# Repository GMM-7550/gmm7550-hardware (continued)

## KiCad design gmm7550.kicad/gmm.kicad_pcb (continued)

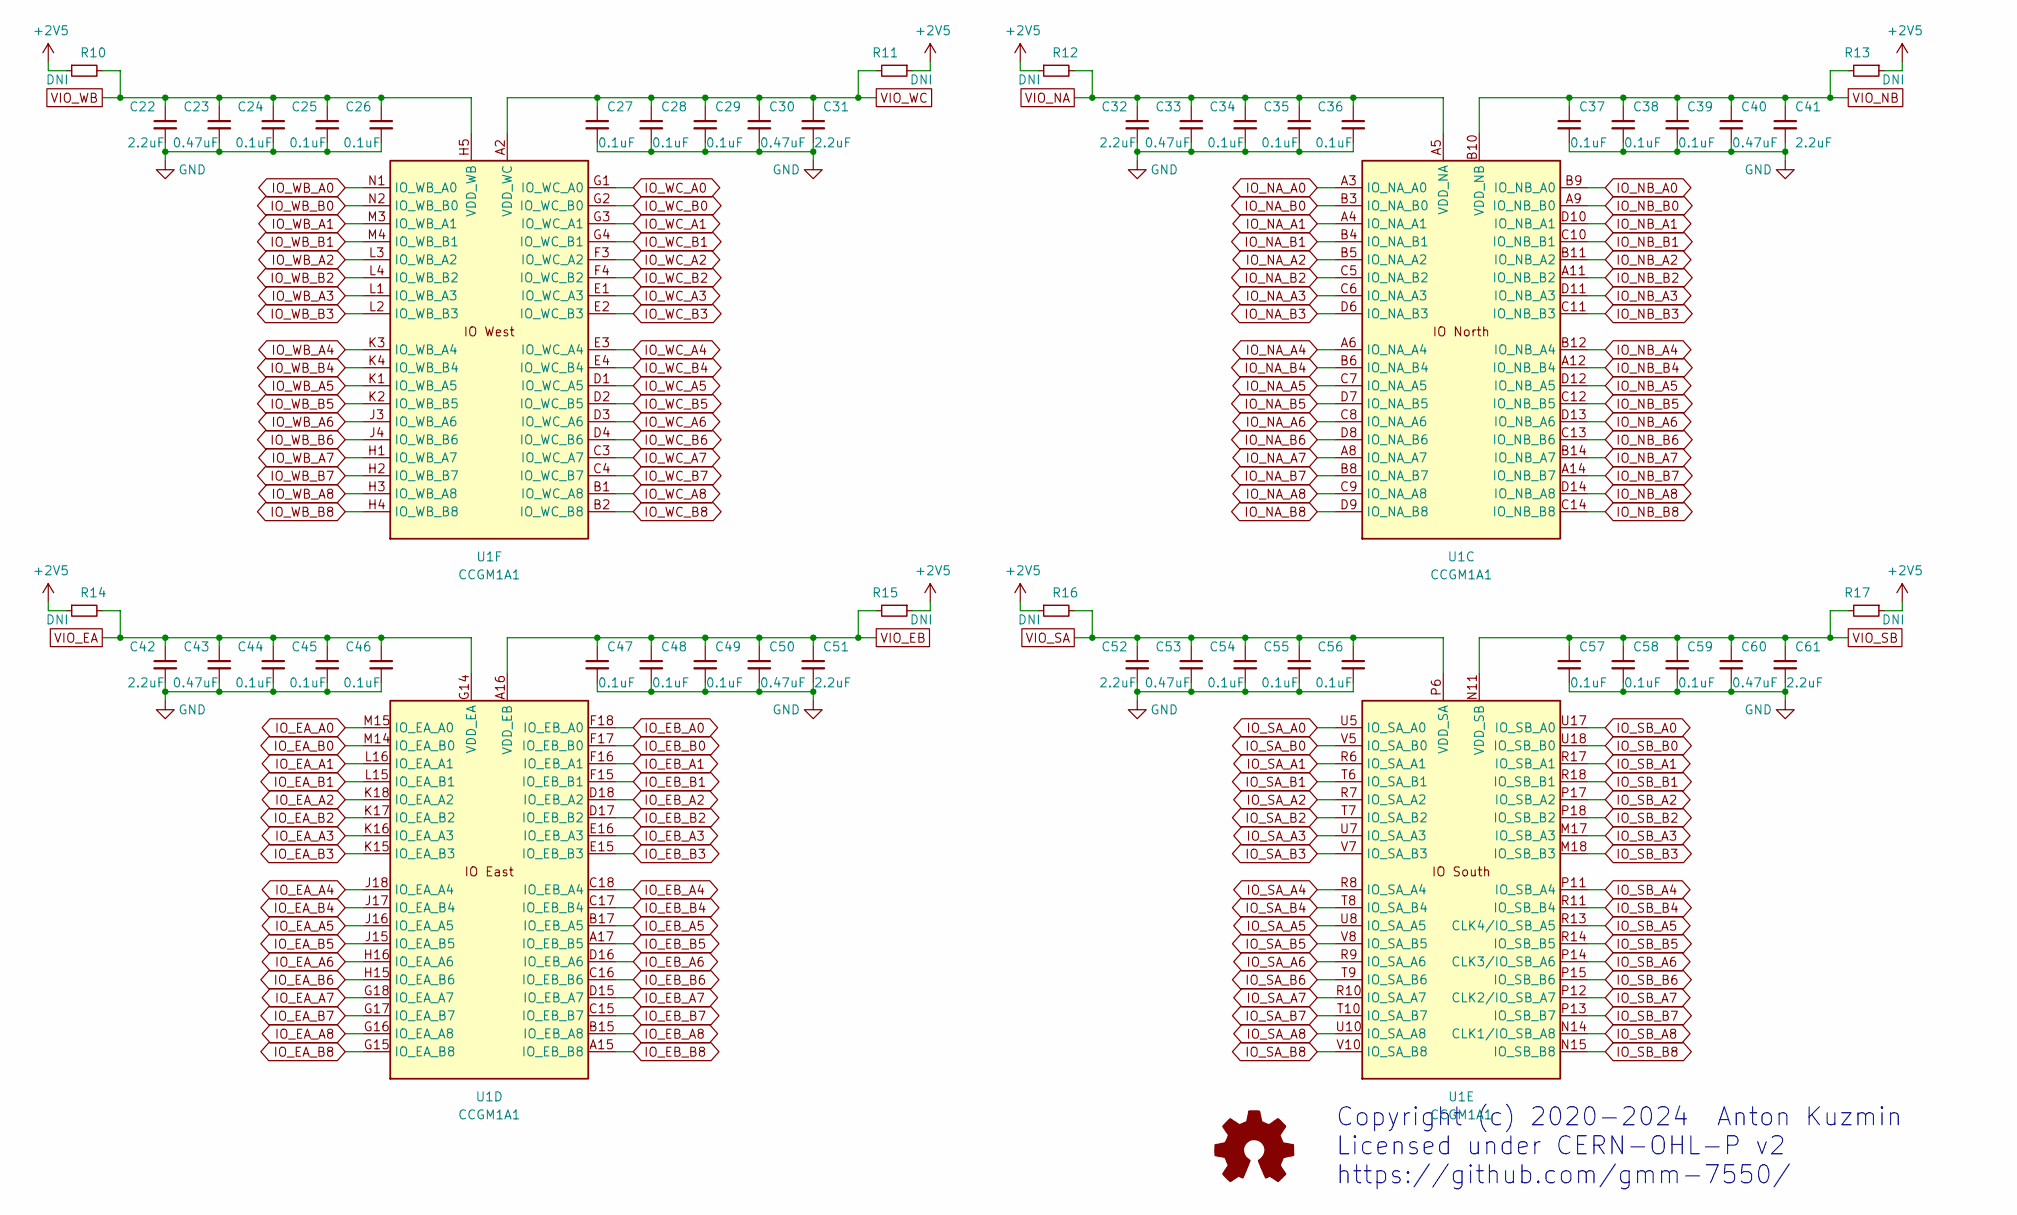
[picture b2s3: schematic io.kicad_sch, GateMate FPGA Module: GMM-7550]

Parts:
C22, C31, C32, C41, C42, C51, C52, C61: 2.2uF; C_0603_1608Metric
C23, C30, C33, C40, C43, C50, C53, C60: 0.47uF; C_0603_1608Metric
C24, C25, C26, C27, C28, C29, C34, C35, C36, C37, C38, C39, C44, C45, C46, C47, C48, C49, C54, C55, C56, C57, C58, C59: 0.1uF; C_0402_1005Metric
R10, R11, R12, R13, R14, R15, R16, R17: DNI; R_0603_1608Metric
U1: CCGM1A1; BGA-324_15.0x15.0mm_Layout18x18_P0.8mm_Ball0.45mm_Pad0.35mm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

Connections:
+2V5: R10.1, R11.1, R12.1, R13.1, R14.1, R15.1, R16.1, R17.1; also elsewhere on the board
GND: C22.2, C23.2, C24.2, C25.2, C26.2, C27.2, C28.2, C29.2, C30.2, C31.2, C32.2, C33.2, C34.2, C35.2, C36.2, C37.2, C38.2, C39.2, C40.2, C41.2, C42.2, C43.2, C44.2, C45.2, C46.2, C47.2, C48.2, C49.2, C50.2, C51.2, C52.2, C53.2, C54.2, C55.2, C56.2, C57.2, C58.2, C59.2, C60.2, C61.2; also elsewhere on the board
IO_EA_A0: U1.M15 (IO_EA_A0); also elsewhere on the board
IO_EA_A1: U1.L16 (IO_EA_A1); also elsewhere on the board
IO_EA_A2: U1.K18 (IO_EA_A2); also elsewhere on the board
IO_EA_A3: U1.K16 (IO_EA_A3); also elsewhere on the board
IO_EA_A4: U1.J18 (IO_EA_A4); also elsewhere on the board
IO_EA_A5: U1.J16 (IO_EA_A5); also elsewhere on the board
IO_EA_A6: U1.H16 (IO_EA_A6); also elsewhere on the board
IO_EA_A7: U1.G18 (IO_EA_A7); also elsewhere on the board
IO_EA_A8: U1.G16 (IO_EA_A8); also elsewhere on the board
IO_EA_B0: U1.M14 (IO_EA_B0); also elsewhere on the board
IO_EA_B1: U1.L15 (IO_EA_B1); also elsewhere on the board
IO_EA_B2: U1.K17 (IO_EA_B2); also elsewhere on the board
IO_EA_B3: U1.K15 (IO_EA_B3); also elsewhere on the board
IO_EA_B4: U1.J17 (IO_EA_B4); also elsewhere on the board
IO_EA_B5: U1.J15 (IO_EA_B5); also elsewhere on the board
IO_EA_B6: U1.H15 (IO_EA_B6); also elsewhere on the board
IO_EA_B7: U1.G17 (IO_EA_B7); also elsewhere on the board
IO_EA_B8: U1.G15 (IO_EA_B8); also elsewhere on the board
IO_EB_A0: U1.F18 (IO_EB_A0); also elsewhere on the board
IO_EB_A1: U1.F16 (IO_EB_A1); also elsewhere on the board
IO_EB_A2: U1.D18 (IO_EB_A2); also elsewhere on the board
IO_EB_A3: U1.E16 (IO_EB_A3); also elsewhere on the board
IO_EB_A4: U1.C18 (IO_EB_A4); also elsewhere on the board
IO_EB_A5: U1.B17 (IO_EB_A5); also elsewhere on the board
IO_EB_A6: U1.D16 (IO_EB_A6); also elsewhere on the board
IO_EB_A7: U1.D15 (IO_EB_A7); also elsewhere on the board
IO_EB_A8: U1.B15 (IO_EB_A8); also elsewhere on the board
IO_EB_B0: U1.F17 (IO_EB_B0); also elsewhere on the board
IO_EB_B1: U1.F15 (IO_EB_B1); also elsewhere on the board
IO_EB_B2: U1.D17 (IO_EB_B2); also elsewhere on the board
IO_EB_B3: U1.E15 (IO_EB_B3); also elsewhere on the board
IO_EB_B4: U1.C17 (IO_EB_B4); also elsewhere on the board
IO_EB_B5: U1.A17 (IO_EB_B5); also elsewhere on the board
IO_EB_B6: U1.C16 (IO_EB_B6); also elsewhere on the board
IO_EB_B7: U1.C15 (IO_EB_B7); also elsewhere on the board
IO_EB_B8: U1.A15 (IO_EB_B8); also elsewhere on the board
IO_NA_A0: U1.A3 (IO_NA_A0); also elsewhere on the board
IO_NA_A1: U1.A4 (IO_NA_A1); also elsewhere on the board
IO_NA_A2: U1.B5 (IO_NA_A2); also elsewhere on the board
IO_NA_A3: U1.C6 (IO_NA_A3); also elsewhere on the board
IO_NA_A4: U1.A6 (IO_NA_A4); also elsewhere on the board
IO_NA_A5: U1.C7 (IO_NA_A5); also elsewhere on the board
IO_NA_A6: U1.C8 (IO_NA_A6); also elsewhere on the board
IO_NA_A7: U1.A8 (IO_NA_A7); also elsewhere on the board
IO_NA_A8: U1.C9 (IO_NA_A8); also elsewhere on the board
IO_NA_B0: U1.B3 (IO_NA_B0); also elsewhere on the board
IO_NA_B1: U1.B4 (IO_NA_B1); also elsewhere on the board
IO_NA_B2: U1.C5 (IO_NA_B2); also elsewhere on the board
IO_NA_B3: U1.D6 (IO_NA_B3); also elsewhere on the board
IO_NA_B4: U1.B6 (IO_NA_B4); also elsewhere on the board
IO_NA_B5: U1.D7 (IO_NA_B5); also elsewhere on the board
IO_NA_B6: U1.D8 (IO_NA_B6); also elsewhere on the board
IO_NA_B7: U1.B8 (IO_NA_B7); also elsewhere on the board
IO_NA_B8: U1.D9 (IO_NA_B8); also elsewhere on the board
IO_NB_A0: U1.B9 (IO_NB_A0); also elsewhere on the board
IO_NB_A1: U1.D10 (IO_NB_A1); also elsewhere on the board
IO_NB_A2: U1.B11 (IO_NB_A2); also elsewhere on the board
IO_NB_A3: U1.D11 (IO_NB_A3); also elsewhere on the board
IO_NB_A4: U1.B12 (IO_NB_A4); also elsewhere on the board
IO_NB_A5: U1.D12 (IO_NB_A5); also elsewhere on the board
IO_NB_A6: U1.D13 (IO_NB_A6); also elsewhere on the board
IO_NB_A7: U1.B14 (IO_NB_A7); also elsewhere on the board
IO_NB_A8: U1.D14 (IO_NB_A8); also elsewhere on the board
IO_NB_B0: U1.A9 (IO_NB_B0); also elsewhere on the board
IO_NB_B1: U1.C10 (IO_NB_B1); also elsewhere on the board
IO_NB_B2: U1.A11 (IO_NB_B2); also elsewhere on the board
IO_NB_B3: U1.C11 (IO_NB_B3); also elsewhere on the board
IO_NB_B4: U1.A12 (IO_NB_B4); also elsewhere on the board
IO_NB_B5: U1.C12 (IO_NB_B5); also elsewhere on the board
IO_NB_B6: U1.C13 (IO_NB_B6); also elsewhere on the board
IO_NB_B7: U1.A14 (IO_NB_B7); also elsewhere on the board
IO_NB_B8: U1.C14 (IO_NB_B8); also elsewhere on the board
IO_SA_A0: U1.U5 (IO_SA_A0); also elsewhere on the board
IO_SA_A1: U1.R6 (IO_SA_A1); also elsewhere on the board
IO_SA_A2: U1.R7 (IO_SA_A2); also elsewhere on the board
IO_SA_A3: U1.U7 (IO_SA_A3); also elsewhere on the board
IO_SA_A4: U1.R8 (IO_SA_A4); also elsewhere on the board
IO_SA_A5: U1.U8 (IO_SA_A5); also elsewhere on the board
IO_SA_A6: U1.R9 (IO_SA_A6); also elsewhere on the board
IO_SA_A7: U1.R10 (IO_SA_A7); also elsewhere on the board
IO_SA_A8: U1.U10 (IO_SA_A8); also elsewhere on the board
IO_SA_B0: U1.V5 (IO_SA_B0); also elsewhere on the board
IO_SA_B1: U1.T6 (IO_SA_B1); also elsewhere on the board
IO_SA_B2: U1.T7 (IO_SA_B2); also elsewhere on the board
IO_SA_B3: U1.V7 (IO_SA_B3); also elsewhere on the board
IO_SA_B4: U1.T8 (IO_SA_B4); also elsewhere on the board
IO_SA_B5: U1.V8 (IO_SA_B5); also elsewhere on the board
IO_SA_B6: U1.T9 (IO_SA_B6); also elsewhere on the board
IO_SA_B7: U1.T10 (IO_SA_B7); also elsewhere on the board
IO_SA_B8: U1.V10 (IO_SA_B8); also elsewhere on the board
IO_SB_A0: U1.U17 (IO_SB_A0); also elsewhere on the board
IO_SB_A1: U1.R17 (IO_SB_A1); also elsewhere on the board
IO_SB_A2: U1.P17 (IO_SB_A2); also elsewhere on the board
IO_SB_A3: U1.M17 (IO_SB_A3); also elsewhere on the board
IO_SB_A4: U1.P11 (IO_SB_A4); also elsewhere on the board
IO_SB_A5: U1.R13 (CLK4/IO_SB_A5); also elsewhere on the board
IO_SB_A6: U1.P14 (CLK3/IO_SB_A6); also elsewhere on the board
IO_SB_A7: U1.P12 (CLK2/IO_SB_A7); also elsewhere on the board
IO_SB_A8: U1.N14 (CLK1/IO_SB_A8); also elsewhere on the board
IO_SB_B0: U1.U18 (IO_SB_B0); also elsewhere on the board
IO_SB_B1: U1.R18 (IO_SB_B1); also elsewhere on the board
IO_SB_B2: U1.P18 (IO_SB_B2); also elsewhere on the board
IO_SB_B3: U1.M18 (IO_SB_B3); also elsewhere on the board
IO_SB_B4: U1.R11 (IO_SB_B4); also elsewhere on the board
IO_SB_B5: U1.R14 (IO_SB_B5); also elsewhere on the board
IO_SB_B6: U1.P15 (IO_SB_B6); also elsewhere on the board
IO_SB_B7: U1.P13 (IO_SB_B7); also elsewhere on the board
IO_SB_B8: U1.N15 (IO_SB_B8); also elsewhere on the board
IO_WB_A0: U1.N1 (IO_WB_A0); also elsewhere on the board
IO_WB_A1: U1.M3 (IO_WB_A1); also elsewhere on the board
IO_WB_A2: U1.L3 (IO_WB_A2); also elsewhere on the board
IO_WB_A3: U1.L1 (IO_WB_A3); also elsewhere on the board
IO_WB_A4: U1.K3 (IO_WB_A4); also elsewhere on the board
IO_WB_A5: U1.K1 (IO_WB_A5); also elsewhere on the board
IO_WB_A6: U1.J3 (IO_WB_A6); also elsewhere on the board
IO_WB_A7: U1.H1 (IO_WB_A7); also elsewhere on the board
IO_WB_A8: U1.H3 (IO_WB_A8); also elsewhere on the board
IO_WB_B0: U1.N2 (IO_WB_B0); also elsewhere on the board
IO_WB_B1: U1.M4 (IO_WB_B1); also elsewhere on the board
IO_WB_B2: U1.L4 (IO_WB_B2); also elsewhere on the board
IO_WB_B3: U1.L2 (IO_WB_B3); also elsewhere on the board
IO_WB_B4: U1.K4 (IO_WB_B4); also elsewhere on the board
IO_WB_B5: U1.K2 (IO_WB_B5); also elsewhere on the board
IO_WB_B6: U1.J4 (IO_WB_B6); also elsewhere on the board
IO_WB_B7: U1.H2 (IO_WB_B7); also elsewhere on the board
IO_WB_B8: U1.H4 (IO_WB_B8); also elsewhere on the board
IO_WC_A0: U1.G1 (IO_WC_A0); also elsewhere on the board
IO_WC_A1: U1.G3 (IO_WC_A1); also elsewhere on the board
IO_WC_A2: U1.F3 (IO_WC_A2); also elsewhere on the board
IO_WC_A3: U1.E1 (IO_WC_A3); also elsewhere on the board
IO_WC_A4: U1.E3 (IO_WC_A4); also elsewhere on the board
IO_WC_A5: U1.D1 (IO_WC_A5); also elsewhere on the board
IO_WC_A6: U1.D3 (IO_WC_A6); also elsewhere on the board
IO_WC_A7: U1.C3 (IO_WC_A7); also elsewhere on the board
IO_WC_A8: U1.B1 (IO_WC_A8); also elsewhere on the board
IO_WC_B0: U1.G2 (IO_WC_B0); also elsewhere on the board
IO_WC_B1: U1.G4 (IO_WC_B1); also elsewhere on the board
IO_WC_B2: U1.F4 (IO_WC_B2); also elsewhere on the board
IO_WC_B3: U1.E2 (IO_WC_B3); also elsewhere on the board
IO_WC_B4: U1.E4 (IO_WC_B4); also elsewhere on the board
IO_WC_B5: U1.D2 (IO_WC_B5); also elsewhere on the board
IO_WC_B6: U1.D4 (IO_WC_B6); also elsewhere on the board
IO_WC_B7: U1.C4 (IO_WC_B7); also elsewhere on the board
IO_WC_B8: U1.B2 (IO_WC_B8); also elsewhere on the board
VIO_EA: C42.1, C43.1, C44.1, C45.1, C46.1, R14.2, U1.G14 (VDD_EA), U1.H17 (VDD_EA), U1.J14 (VDD_EA), U1.L14 (VDD_EA), U1.L17 (VDD_EA); also elsewhere on the board
VIO_EB: C47.1, C48.1, C49.1, C50.1, C51.1, R15.2, U1.A16 (VDD_EB), U1.B18 (VDD_EB), U1.E14 (VDD_EB), U1.E17 (VDD_EB), U1.F13 (VDD_EB); also elsewhere on the board
VIO_NA: C32.1, C33.1, C34.1, C35.1, C36.1, R12.2, U1.A5 (VDD_NA), U1.B7 (VDD_NA), U1.E6 (VDD_NA), U1.E8 (VDD_NA), U1.F7 (VDD_NA); also elsewhere on the board
VIO_NB: C37.1, C38.1, C39.1, C40.1, C41.1, R13.2, U1.B10 (VDD_NB), U1.B13 (VDD_NB), U1.E10 (VDD_NB), U1.E12 (VDD_NB), U1.F11 (VDD_NB); also elsewhere on the board
VIO_SA: C52.1, C53.1, C54.1, C55.1, C56.1, R16.2, U1.P6 (VDD_SA), U1.P8 (VDD_SA), U1.P10 (VDD_SA), U1.U6 (VDD_SA), U1.U9 (VDD_SA); also elsewhere on the board
VIO_SB: C57.1, C58.1, C59.1, C60.1, C61.1, R17.2, U1.N11 (VDD_SB), U1.N13 (VDD_SB), U1.N18 (VDD_SB), U1.R15 (VDD_SB), U1.T18 (VDD_SB); also elsewhere on the board
VIO_WB: C22.1, C23.1, C24.1, C25.1, C26.1, R10.2, U1.H5 (VDD_WB), U1.J2 (VDD_WB), U1.K5 (VDD_WB), U1.M2 (VDD_WB), U1.M5 (VDD_WB); also elsewhere on the board
VIO_WC: C27.1, C28.1, C29.1, C30.1, C31.1, R11.2, U1.A2 (VDD_WC), U1.C2 (VDD_WC), U1.D5 (VDD_WC), U1.F2 (VDD_WC), U1.F5 (VDD_WC); also elsewhere on the board

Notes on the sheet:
Copyright (c) 2020-2024 Anton Kuzmin Licensed under CERN-OHL-P v2 https://github.com/gmm-7550/

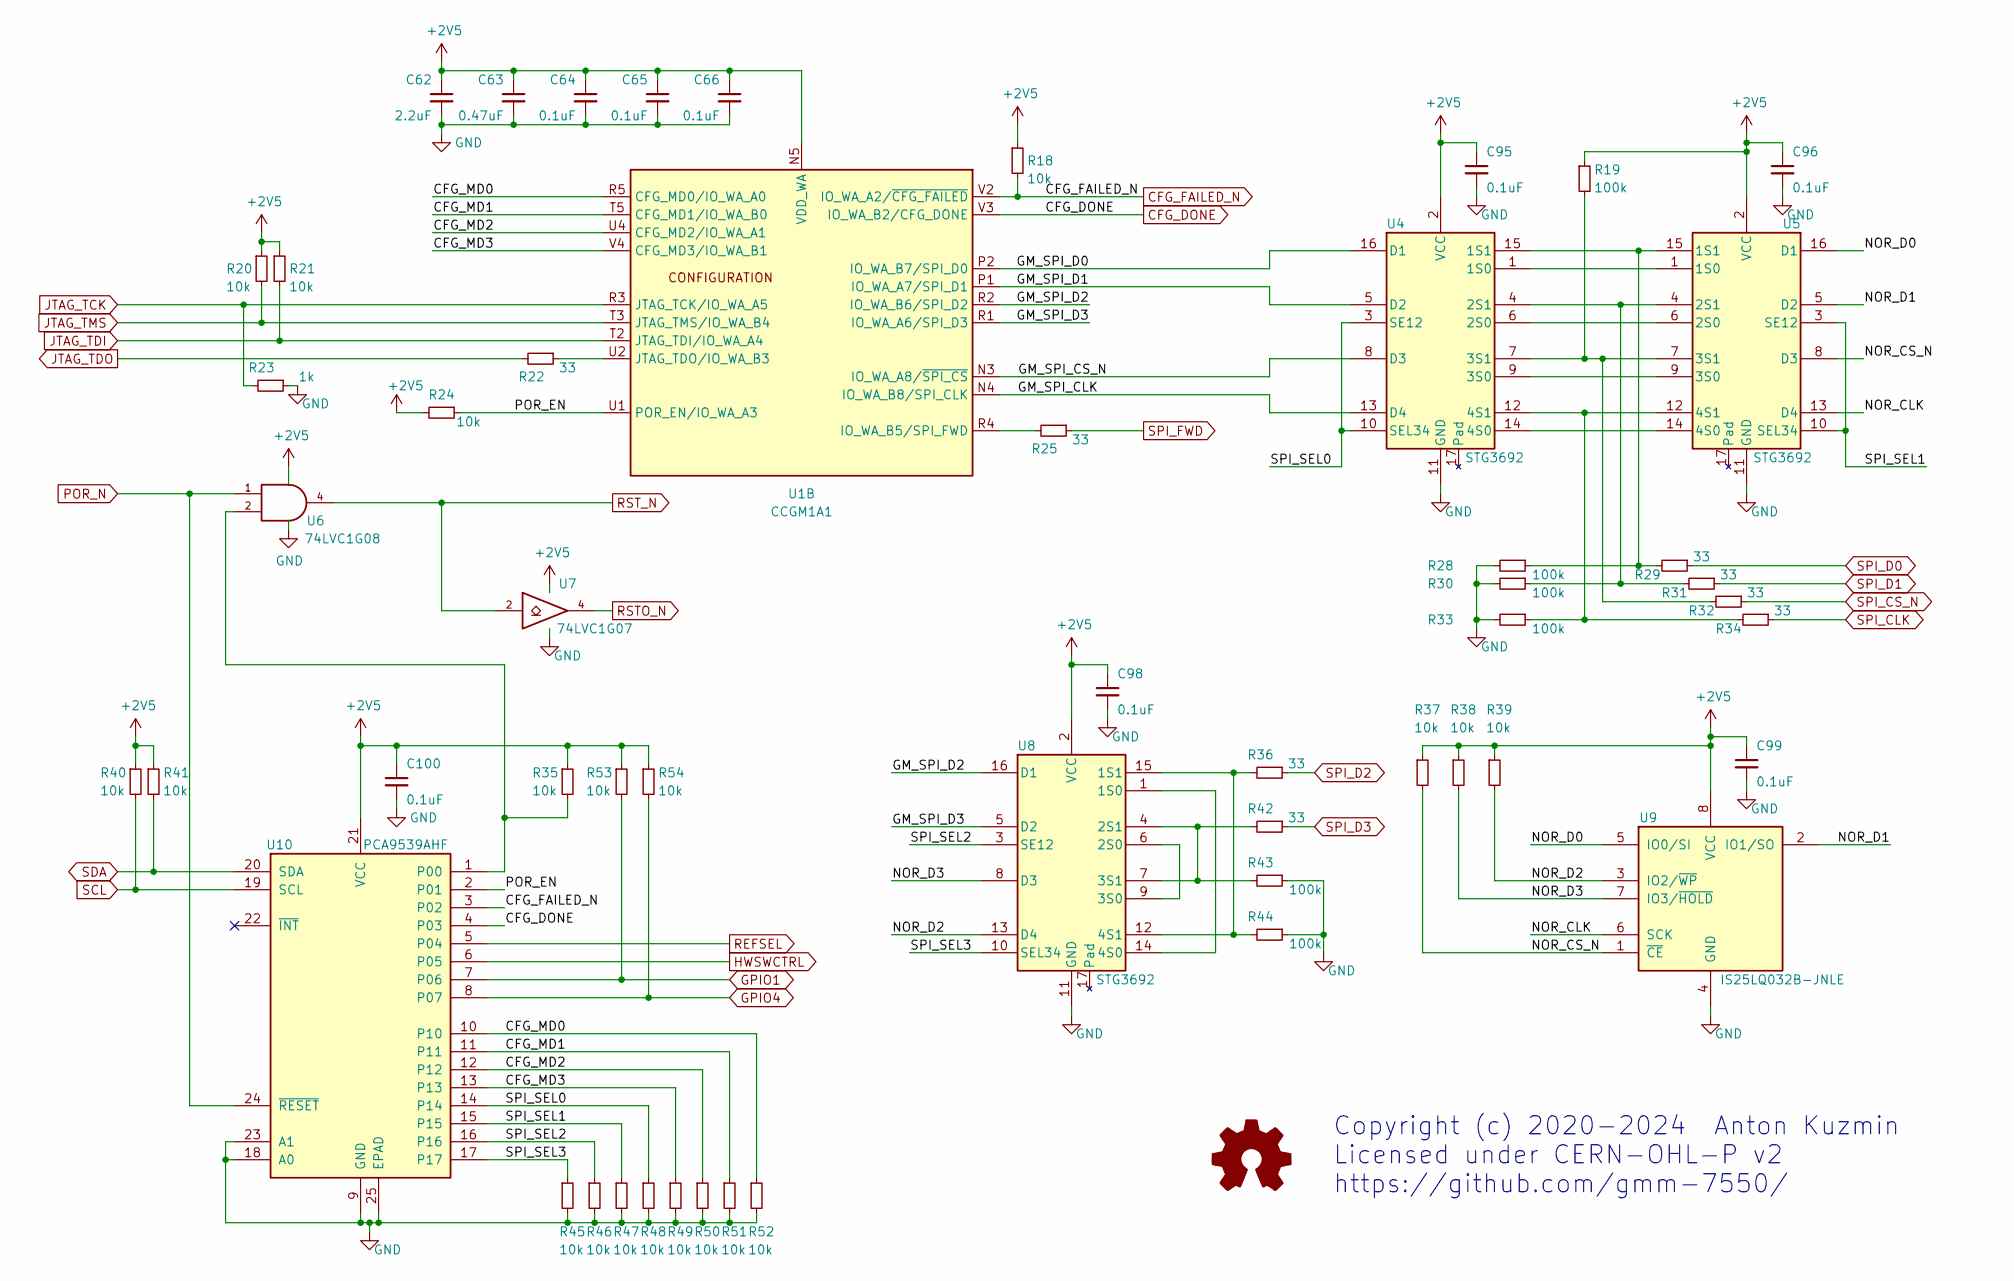
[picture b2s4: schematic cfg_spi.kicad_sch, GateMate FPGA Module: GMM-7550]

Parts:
C62: 2.2uF; C_0805_2012Metric
C63: 0.47uF; C_0603_1608Metric
C64, C65, C66, C95, C96, C98, C99, C100: 0.1uF; C_0402_1005Metric
R18, R20, R21, R24, R35, R37, R38, R39, R40, R41, R45, R46, R47, R48, R49, R50, R51, R52, R53, R54: 10k; R_0402_1005Metric
R19, R28, R30, R33, R43, R44: 100k; R_0402_1005Metric
R22, R25, R29, R31, R32, R34, R36, R42: 33; R_0402_1005Metric
R23: 1k; R_0402_1005Metric
U1: CCGM1A1; BGA-324_15.0x15.0mm_Layout18x18_P0.8mm_Ball0.45mm_Pad0.35mm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
U4, U5, U8: STG3692; QFN-16-1EP_2.6x1.8mm_P0.4mm_EP1.5x0.7mm
U6: 74LVC1G08; SOT-353_SC-70-5
U7: 74LVC1G07; SOT-23-5
U9: IS25LQ032B-JNLE; SO-8_3.9x4.9mm_P1.27mm
U10: PCA9539AHF; Texas_S-PVQFN-N24_EP2.1x2.1mm

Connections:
+2V5: C62.1, C63.1, C64.1, C65.1, C66.1, C95.1, C96.1, C98.1, C99.1, C100.1, R18.1, R19.1, R20.1, R21.1, R24.2, R35.1, R37.1, R38.1, R39.1, R40.1, R41.1, R53.1, R54.1, U1.N5 (VDD_WA), U1.P3 (VDD_WA), U1.P5 (VDD_WA), U1.T1 (VDD_WA), U1.U3 (VDD_WA), U4.2 (VCC), U5.2 (VCC), U6.5 (VCC), U7.5 (VCC), U8.2 (VCC), U9.8 (VCC), U10.21 (VCC); also elsewhere on the board
/Configuration and Control/CFG_MD0: R52.1, U1.R5 (CFG_MD0/IO_WA_A0), U10.10
/Configuration and Control/CFG_MD1: R51.1, U1.T5 (CFG_MD1/IO_WA_B0), U10.11
/Configuration and Control/CFG_MD2: R50.1, U1.U4 (CFG_MD2/IO_WA_A1), U10.12
/Configuration and Control/CFG_MD3: R49.1, U1.V4 (CFG_MD3/IO_WA_B1), U10.13
/Configuration and Control/GM_SPI_CLK: U1.N4 (IO_WA_B8/SPI_CLK), U4.13 (D4)
/Configuration and Control/GM_SPI_CS_N: U1.N3 (IO_WA_A8/~SPI_CS), U4.8 (D3)
/Configuration and Control/GM_SPI_D0: U1.P2 (IO_WA_B7/SPI_D0), U4.16 (D1)
/Configuration and Control/GM_SPI_D1: U1.P1 (IO_WA_A7/SPI_D1), U4.5 (D2)
/Configuration and Control/GM_SPI_D2: U1.R2 (IO_WA_B6/SPI_D2), U8.16 (D1)
/Configuration and Control/GM_SPI_D3: U1.R1 (IO_WA_A6/SPI_D3), U8.5 (D2)
/Configuration and Control/NOR_CLK: U5.13 (D4), U9.6 (SCK)
/Configuration and Control/NOR_CS_N: R37.2, U5.8 (D3), U9.1 (~CE)
/Configuration and Control/NOR_D0: U5.16 (D1), U9.5 (IO0/SI)
/Configuration and Control/NOR_D1: U5.5 (D2), U9.2 (IO1/SO)
/Configuration and Control/NOR_D2: R39.2, U8.13 (D4), U9.3 (IO2/~WP)
/Configuration and Control/NOR_D3: R38.2, U8.8 (D3), U9.7 (IO3/~HOLD)
/Configuration and Control/POR_EN: R24.1, U1.U1 (POR_EN/IO_WA_A3), U10.2 (P01)
/Configuration and Control/SPI_SEL0: R48.1, U4.3 (SE12), U4.10 (SEL34), U10.14
/Configuration and Control/SPI_SEL1: R47.1, U5.3 (SE12), U5.10 (SEL34), U10.15
/Configuration and Control/SPI_SEL2: R46.1, U8.3 (SE12), U10.16
/Configuration and Control/SPI_SEL3: R45.1, U8.10 (SEL34), U10.17
CFG_DONE: U1.V3 (IO_WA_B2/CFG_DONE), U10.4 (P03); also elsewhere on the board
CFG_FAILED_N: R18.2, U1.V2 (IO_WA_A2/~CFG_FAILED), U10.3 (P02); also elsewhere on the board
GND: C62.2, C63.2, C64.2, C65.2, C66.2, C95.2, C96.2, C98.2, C99.2, C100.2, R23.1, R28.2, R30.2, R33.2, R43.1, R44.1, R45.2, R46.2, R47.2, R48.2, R49.2, R50.2, R51.2, R52.2, U4.11 (GND), U5.11 (GND), U6.3 (GND), U7.3 (GND), U8.11 (GND), U9.4 (GND), U10.9 (GND), U10.18 (A0), U10.23 (A1), U10.25 (EPAD); also elsewhere on the board
GPIO1: R53.2, U10.7 (P06); also elsewhere on the board
GPIO4: R54.2, U10.8 (P07); also elsewhere on the board
HWSWCTRL: U10.6 (P05); also elsewhere on the board
JTAG_TCK: R23.2, U1.R3 (JTAG_TCK/IO_WA_A5); also elsewhere on the board
JTAG_TDI: R21.2, U1.T2 (JTAG_TDI/IO_WA_A4); also elsewhere on the board
JTAG_TDO: R22.2; also elsewhere on the board
JTAG_TMS: R20.2, U1.T3 (JTAG_TMS/IO_WA_B4); also elsewhere on the board
unnamed: R25.2, U1.R4 (IO_WA_B5/SPI_FWD)
unnamed: R22.1, U1.U2 (JTAG_TDO/IO_WA_B3)
unnamed: U4.1 (1S0), U5.1 (1S0)
unnamed: R28.1, R29.2, U4.15 (1S1), U5.15 (1S1)
unnamed: U4.6 (2S0), U5.6 (2S0)
unnamed: R30.1, R31.2, U4.4 (2S1), U5.4 (2S1)
unnamed: U4.9 (3S0), U5.9 (3S0)
unnamed: R19.2, R32.2, U4.7 (3S1), U5.7 (3S1)
unnamed: U4.14 (4S0), U5.14 (4S0)
unnamed: R33.1, R34.2, U4.12 (4S1), U5.12 (4S1)
unnamed: U8.1 (1S0), U8.14 (4S0)
unnamed: R36.2, R44.2, U8.12 (4S1), U8.15 (1S1)
unnamed: U8.6 (2S0), U8.9 (3S0)
unnamed: R42.2, R43.2, U8.4 (2S1), U8.7 (3S1)
unnamed: R35.2, U6.2, U10.1 (P00)
POR_N: U6.1, U10.24 (~RESET); also elsewhere on the board
REFSEL: U10.5 (P04); also elsewhere on the board
RSTO_N: U7.4; also elsewhere on the board
RST_N: U6.4, U7.2; also elsewhere on the board
SCL: R40.2, U10.19 (SCL); also elsewhere on the board
SDA: R41.2, U10.20 (SDA); also elsewhere on the board
SPI_CLK: R34.1; also elsewhere on the board
SPI_CS_N: R32.1; also elsewhere on the board
SPI_D0: R29.1; also elsewhere on the board
SPI_D1: R31.1; also elsewhere on the board
SPI_D2: R36.1; also elsewhere on the board
SPI_D3: R42.1; also elsewhere on the board
SPI_FWD: R25.1; also elsewhere on the board

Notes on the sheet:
Copyright (c) 2020-2024 Anton Kuzmin Licensed under CERN-OHL-P v2 https://github.com/gmm-7550/

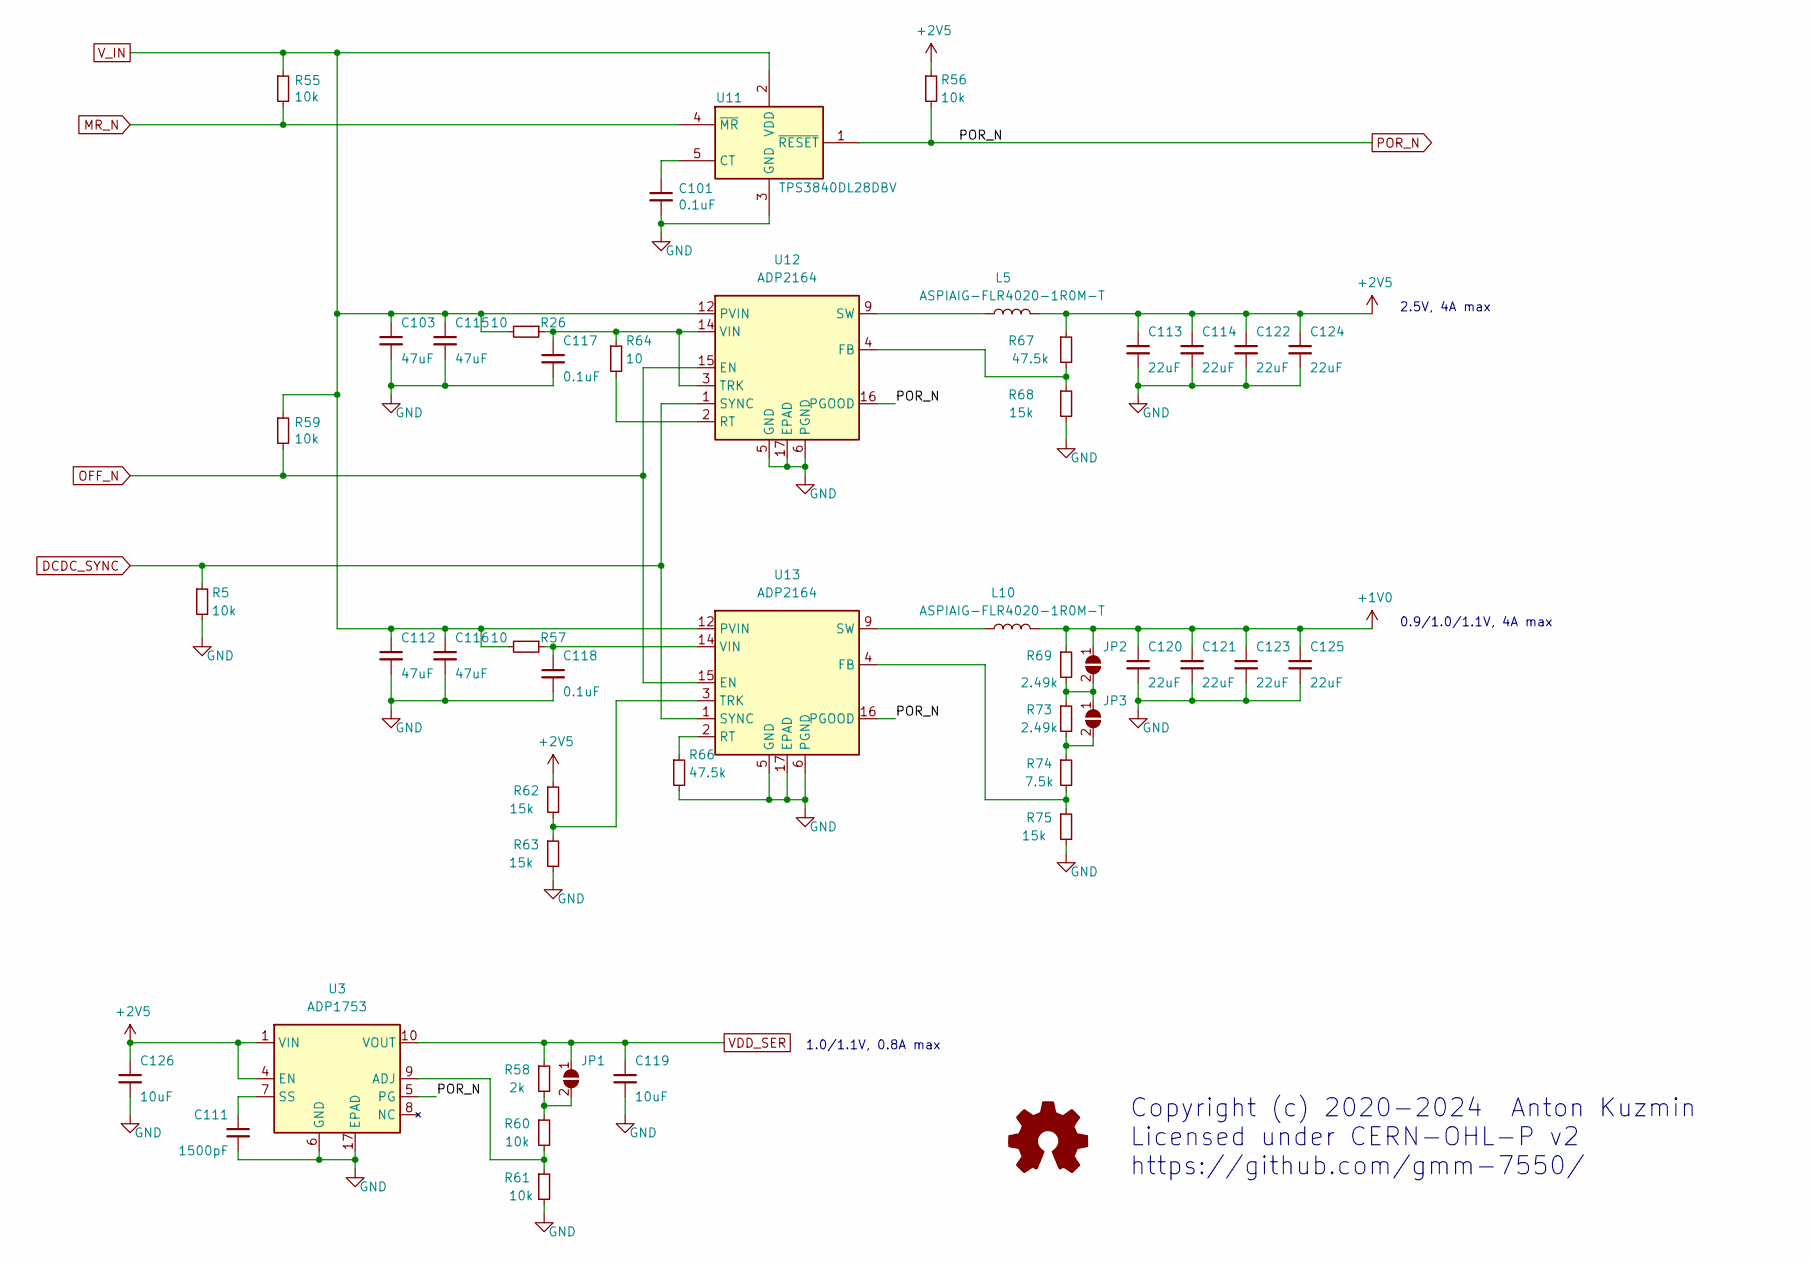
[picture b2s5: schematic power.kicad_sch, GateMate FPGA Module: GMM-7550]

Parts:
C101, C117, C118: 0.1uF; C_0402_1005Metric
C103, C112, C115, C116: 47uF; C_1210_3225Metric
C111: 1500pF; C_0402_1005Metric
C113, C114, C120, C121, C122, C123, C124, C125: 22uF; C_1206_3216Metric
C119, C126: 10uF; C_0805_2012Metric
JP1, JP2, JP3: SolderJumper_2_Open_Small; SolderJumper-2_P1.3mm_Open_RoundedPad1.0x1.5mm
L5, L10: ASPIAIG-FLR4020-1R0M-T; L_Abracon_F4020_4.1x4.1mm
R5, R55, R56, R59, R60, R61: 10k; R_0402_1005Metric
R26, R57, R64: 10; R_0402_1005Metric
R58: 2k; R_0402_1005Metric
R62, R63, R68, R75: 15k; R_0402_1005Metric
R66, R67: 47.5k; R_0402_1005Metric
R69, R73: 2.49k; R_0402_1005Metric
R74: 7.5k; R_0402_1005Metric
U3: ADP1753; QFN-16-1EP_4x4mm_P0.65mm_EP2.1x2.1mm_ThermalVias
U11: TPS3840DL28DBV; SOT-23-5
U12, U13: ADP2164; QFN-16-1EP_4x4mm_P0.65mm_EP2.5x2.5mm_ThermalVias

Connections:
+1V0: C120.1, C121.1, C123.1, C125.1, JP2.1, L10.2, R69.1; also elsewhere on the board
+2V5: C113.1, C114.1, C122.1, C124.1, C126.1, L5.2, R56.1, R62.1, R67.1, U3.1 (VIN), U3.2 (VIN), U3.3 (VIN), U3.4 (EN), U3.15 (VIN), U3.16 (VIN); also elsewhere on the board
DCDC_SYNC: R5.1, U12.1 (SYNC), U13.1 (SYNC); also elsewhere on the board
GND: C101.2, C103.2, C111.2, C112.2, C113.2, C114.2, C115.2, C116.2, C117.2, C118.2, C119.2, C120.2, C121.2, C122.2, C123.2, C124.2, C125.2, C126.2, R5.2, R61.2, R63.2, R66.2, R68.2, R75.2, U3.6 (GND), U3.17 (EPAD), U11.3 (GND), U12.5 (GND), U12.6 (PGND), U12.7 (PGND), U12.8 (PGND), U12.17 (EPAD), U13.5 (GND), U13.6 (PGND), U13.7 (PGND), U13.8 (PGND), U13.17 (EPAD); also elsewhere on the board
MR_N: R55.2, U11.4 (~MR); also elsewhere on the board
unnamed: JP1.2, R58.2, R60.1
unnamed: JP2.2, JP3.1, R69.2, R73.1
unnamed: JP3.2, R73.2, R74.1
unnamed: L5.1, U12.9 (SW), U12.10 (SW), U12.11 (SW)
unnamed: L10.1, U13.9 (SW), U13.10 (SW), U13.11 (SW)
unnamed: R60.2, R61.1, U3.9 (ADJ)
unnamed: C111.1, U3.7 (SS)
unnamed: C101.1, U11.5 (CT)
unnamed: R67.2, R68.1, U12.4 (FB)
unnamed: R64.2, U12.2 (RT)
unnamed: C117.1, R26.1, R64.1, U12.3 (TRK), U12.14 (VIN)
unnamed: R74.2, R75.1, U13.4 (FB)
unnamed: R66.1, U13.2 (RT)
unnamed: R62.2, R63.1, U13.3 (TRK)
unnamed: C118.1, R57.1, U13.14 (VIN)
OFF_N: R59.2, U12.15 (EN), U13.15 (EN); also elsewhere on the board
POR_N: R56.2, U3.5 (PG), U11.1 (~RESET), U12.16 (PGOOD), U13.16 (PGOOD); also elsewhere on the board
VDD_SER: C119.1, JP1.1, R58.1, U3.10 (VOUT), U3.11 (VOUT), U3.12 (VOUT), U3.13 (VOUT), U3.14 (VOUT); also elsewhere on the board
V_IN: C103.1, C112.1, C115.1, C116.1, R26.2, R55.1, R57.2, R59.1, U11.2 (VDD), U12.12 (PVIN), U12.13 (PVIN), U13.12 (PVIN), U13.13 (PVIN); also elsewhere on the board

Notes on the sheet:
2.5V, 4A max
1.0/1.1V, 0.8A max
0.9/1.0/1.1V, 4A max
Copyright (c) 2020-2024 Anton Kuzmin Licensed under CERN-OHL-P v2 https://github.com/gmm-7550/

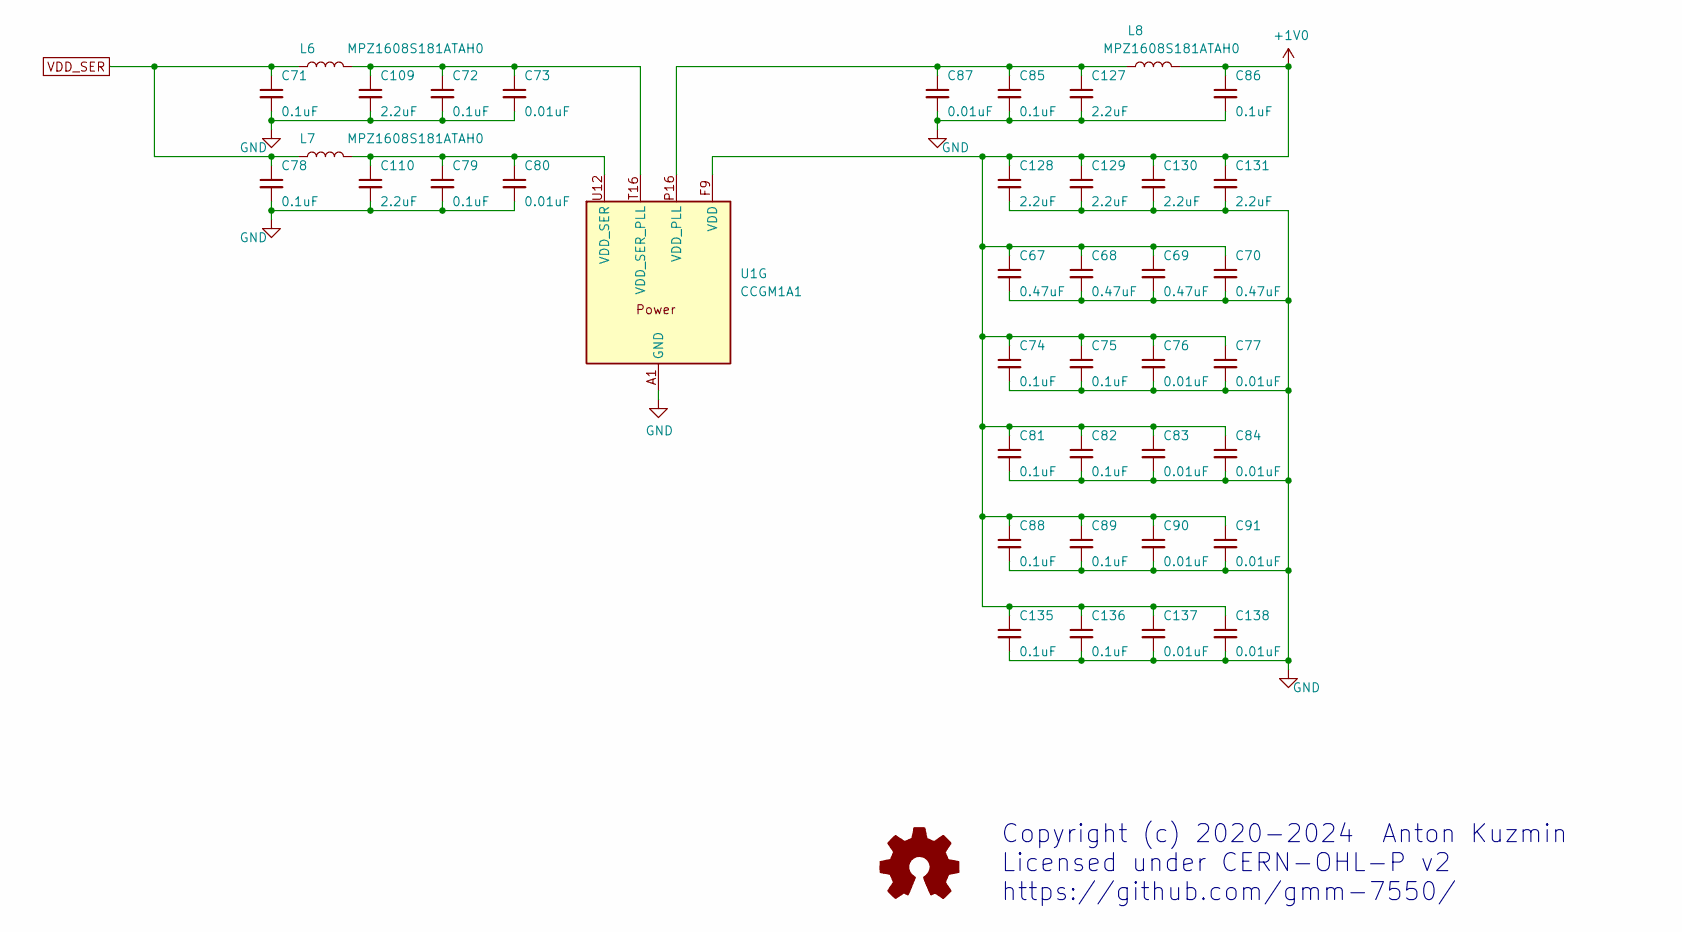
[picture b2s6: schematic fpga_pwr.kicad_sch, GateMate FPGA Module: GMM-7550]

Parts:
C67, C68, C69, C70: 0.47uF; C_0603_1608Metric
C71, C72, C74, C75, C78, C79, C81, C82, C85, C86, C88, C89, C135, C136: 0.1uF; C_0402_1005Metric
C73, C76, C77, C80, C83, C84, C87, C90, C91, C137, C138: 0.01uF; C_0402_1005Metric
C109, C110, C127, C128, C129, C130, C131: 2.2uF; C_0603_1608Metric
L6, L7, L8: MPZ1608S181ATAH0; L_0603_1608Metric
U1: CCGM1A1; BGA-324_15.0x15.0mm_Layout18x18_P0.8mm_Ball0.45mm_Pad0.35mm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

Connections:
+1V0: C67.1, C68.1, C69.1, C70.1, C74.1, C75.1, C76.1, C77.1, C81.1, C82.1, C83.1, C84.1, C86.1, C88.1, C89.1, C90.1, C91.1, C128.1, C129.1, C130.1, C131.1, C135.1, C136.1, C137.1, C138.1, L8.2, U1.F9 (VDD), U1.G6 (VDD), U1.G8 (VDD), U1.G10 (VDD), U1.G12 (VDD), U1.H7 (VDD), U1.H9 (VDD), U1.H11 (VDD), U1.H13 (VDD), U1.J6 (VDD), U1.J8 (VDD), U1.J10 (VDD), U1.J12 (VDD), U1.K7 (VDD), U1.K9 (VDD), U1.K11 (VDD), U1.K13 (VDD), U1.L6 (VDD), U1.L8 (VDD), U1.L10 (VDD), U1.L12 (VDD), U1.M7 (VDD), U1.M9 (VDD), U1.M11 (VDD), U1.M13 (VDD), U1.N6 (VDD), U1.N8 (VDD), U1.N10 (VDD); also elsewhere on the board
GND: C67.2, C68.2, C69.2, C70.2, C71.2, C72.2, C73.2, C74.2, C75.2, C76.2, C77.2, C78.2, C79.2, C80.2, C81.2, C82.2, C83.2, C84.2, C85.2, C86.2, C87.2, C88.2, C89.2, C90.2, C91.2, C109.2, C110.2, C127.2, C128.2, C129.2, C130.2, C131.2, C135.2, C136.2, C137.2, C138.2, U1.A1 (GND), U1.A7 (GND), U1.A10 (GND), U1.A13 (GND), U1.A18 (GND), U1.B16 (GND), U1.C1 (GND), U1.E5 (GND), U1.E7 (GND), U1.E9 (GND), U1.E11 (GND), U1.E13 (GND), U1.E18 (GND), U1.F1 (GND), U1.F6 (GND), U1.F8 (GND), U1.F10 (GND), U1.F12 (GND), U1.F14 (GND), U1.G5 (GND), U1.G7 (GND), U1.G9 (GND), U1.G11 (GND), U1.G13 (GND), U1.H6 (GND), U1.H8 (GND), U1.H10 (GND), U1.H12 (GND), U1.H14 (GND), U1.H18 (GND), U1.J1 (GND), U1.J5 (GND), U1.J7 (GND), U1.J9 (GND), U1.J11 (GND), U1.J13 (GND), U1.K6 (GND), U1.K8 (GND), U1.K10 (GND), U1.K12 (GND), U1.K14 (GND), U1.L5 (GND), U1.L7 (GND), U1.L9 (GND), U1.L11 (GND), U1.L13 (GND), U1.L18 (GND), U1.M1 (GND), U1.M6 (GND), U1.M8 (GND), U1.M10 (GND), U1.M12 (GND), U1.M16 (GND), U1.N7 (GND), U1.N9 (GND), U1.N12 (GND), U1.N17 (GND), U1.P4 (GND), U1.P7 (GND), U1.P9 (GND), U1.R12 (GND), U1.R16 (GND), U1.T4 (GND), U1.T11 (GND), U1.T17 (GND), U1.U14 (GND), U1.U15 (GND), U1.U16 (GND), U1.V1 (GND), U1.V6 (GND), U1.V9 (GND), U1.V14 (GND), U1.V16 (GND), U1.V18 (GND); also elsewhere on the board
unnamed: C79.1, C80.1, C110.1, L7.2, U1.U12 (VDD_SER), U1.V17 (VDD_SER)
unnamed: C85.1, C87.1, C127.1, L8.1, U1.P16 (VDD_PLL)
unnamed: C72.1, C73.1, C109.1, L6.2, U1.T16 (VDD_SER_PLL)
VDD_SER: C71.1, C78.1, L6.1, L7.1; also elsewhere on the board

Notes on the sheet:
Copyright (c) 2020-2024 Anton Kuzmin Licensed under CERN-OHL-P v2 https://github.com/gmm-7550/
